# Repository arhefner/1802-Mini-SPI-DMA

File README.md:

# 1802-Mini-SPI-DMA
SPI Expansion Board for the 1802/Mini Computer

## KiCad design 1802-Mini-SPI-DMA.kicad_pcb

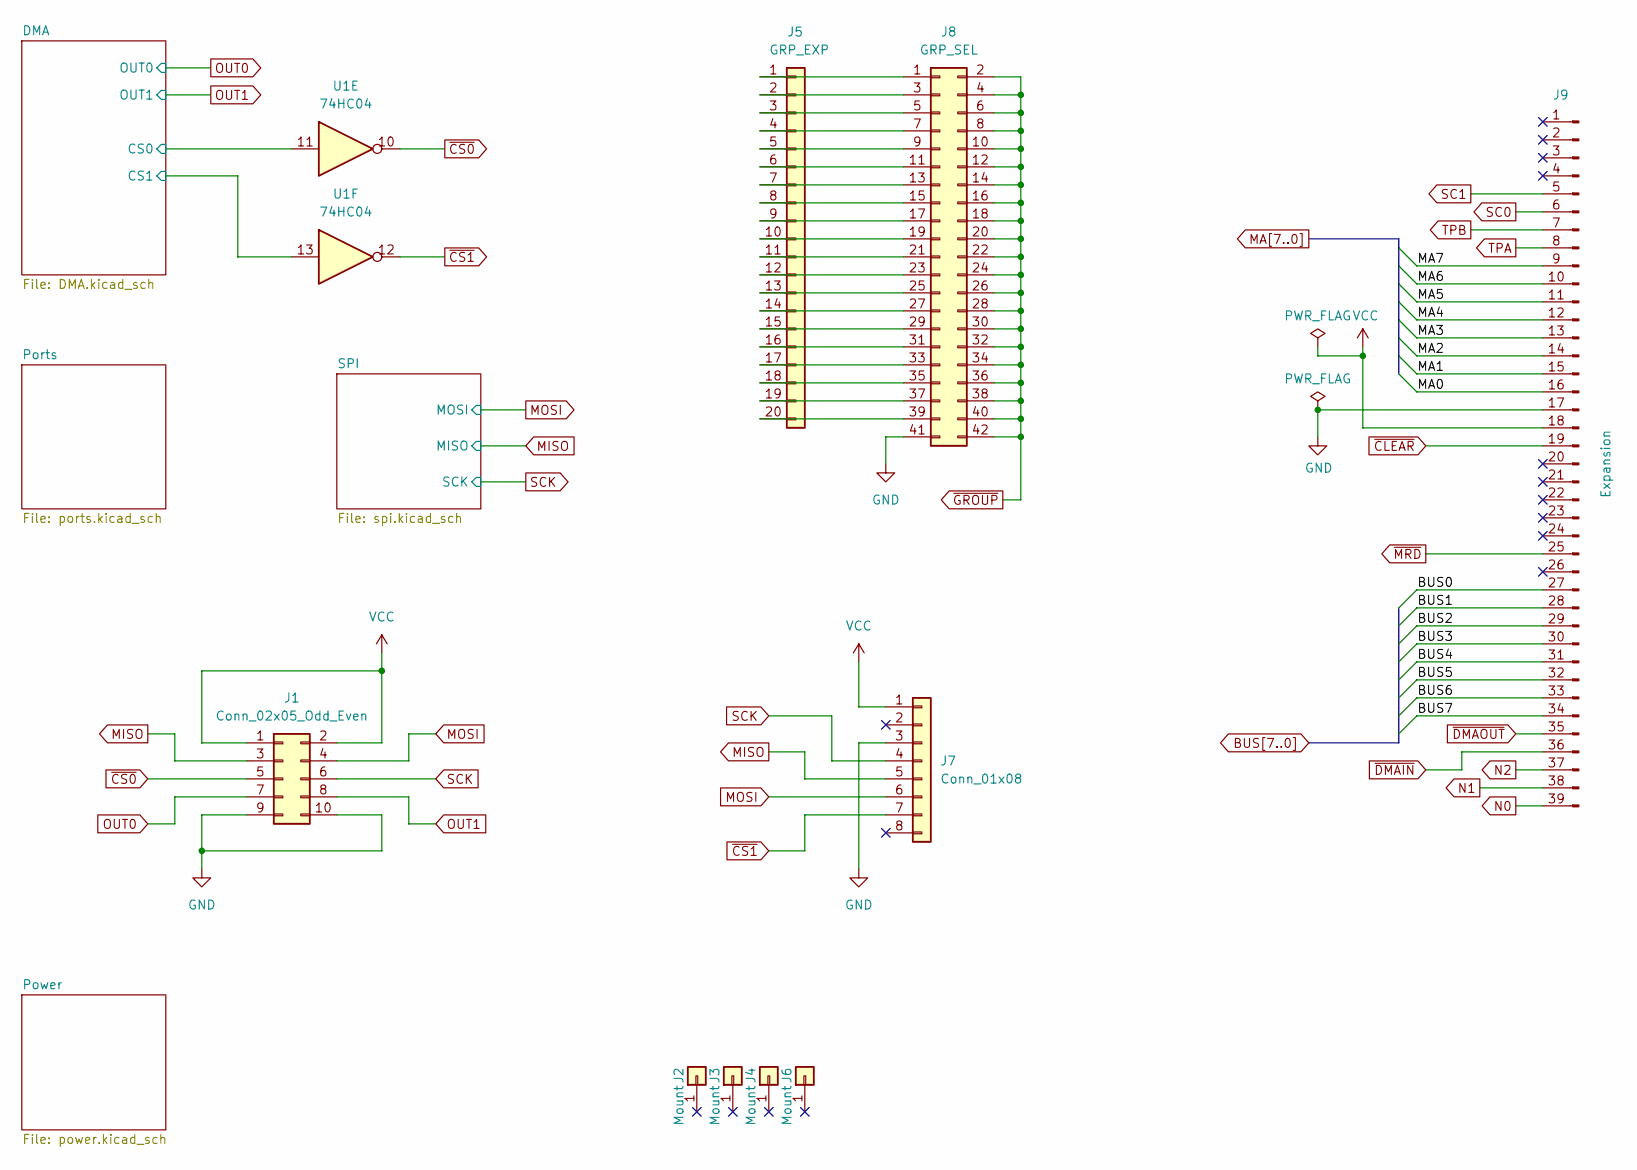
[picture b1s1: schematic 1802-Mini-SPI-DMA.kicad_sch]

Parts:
J1: Conn_02x05_Odd_Even; PinHeader_2x05_P2.54mm_Horizontal
J2, J3, J4, J6: Mount; 1pin
J5: GRP_EXP; PinHeader_1x20_P2.54mm_Vertical
J7: Conn_01x08; Adafruit_micro_sd_adapter
J8: GRP_SEL; PinHeader_2x21_P2.54mm_Vertical
J9: Expansion; Pin_Header_Straight_1x39_Pitch2.54mm
U1: 74HC04; DIP-14_W7.62mm_Socket

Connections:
/DMA/CS0: U1.11; also elsewhere on the board
/DMA/CS1: U1.13; also elsewhere on the board
BUS0: J9.27; also elsewhere on the board
BUS1: J9.28; also elsewhere on the board
BUS2: J9.29; also elsewhere on the board
BUS3: J9.30; also elsewhere on the board
BUS4: J9.31; also elsewhere on the board
BUS5: J9.32; also elsewhere on the board
BUS6: J9.33; also elsewhere on the board
BUS7: J9.34; also elsewhere on the board
GND: J1.9, J1.10, J7.3, J8.41, J9.17; also elsewhere on the board
MA0: J9.16
MA1: J9.15
MA2: J9.14
MA3: J9.13
MA4: J9.12
MA5: J9.11
MA6: J9.10
MA7: J9.9
MISO: J1.3, J7.5; also elsewhere on the board
MOSI: J1.4, J7.6; also elsewhere on the board
N0: J9.39; also elsewhere on the board
N1: J9.38; also elsewhere on the board
N2: J9.37; also elsewhere on the board
unnamed: J5.1, J8.1
unnamed: J5.2, J8.3
unnamed: J5.3, J8.5
unnamed: J5.4, J8.7
unnamed: J5.5, J8.9
unnamed: J5.6, J8.11
unnamed: J5.7, J8.13
unnamed: J5.8, J8.15
unnamed: J5.9, J8.17
unnamed: J5.10, J8.19
unnamed: J5.11, J8.21
unnamed: J5.12, J8.23
unnamed: J5.13, J8.25
unnamed: J5.14, J8.27
unnamed: J5.15, J8.29
unnamed: J5.16, J8.31
unnamed: J5.17, J8.33
unnamed: J5.18, J8.35
unnamed: J5.19, J8.37
unnamed: J5.20, J8.39
OUT0: J1.7; also elsewhere on the board
OUT1: J1.8; also elsewhere on the board
SC0: J9.6; also elsewhere on the board
SC1: J9.5; also elsewhere on the board
SCK: J1.6, J7.4; also elsewhere on the board
TPA: J9.8; also elsewhere on the board
TPB: J9.7; also elsewhere on the board
VCC: J1.1, J1.2, J7.1, J9.18; also elsewhere on the board
~CLEAR: J9.19; also elsewhere on the board
~CS0: J1.5, U1.10
~CS1: J7.7, U1.12
~DMAIN: J9.36; also elsewhere on the board
~DMAOUT: J9.35; also elsewhere on the board
~GROUP: J8.2, J8.4, J8.6, J8.8, J8.10, J8.12, J8.14, J8.16, J8.18, J8.20, J8.22, J8.24, J8.26, J8.28, J8.30, J8.32, J8.34, J8.36, J8.38, J8.40, J8.42; also elsewhere on the board
~MRD: J9.25; also elsewhere on the board

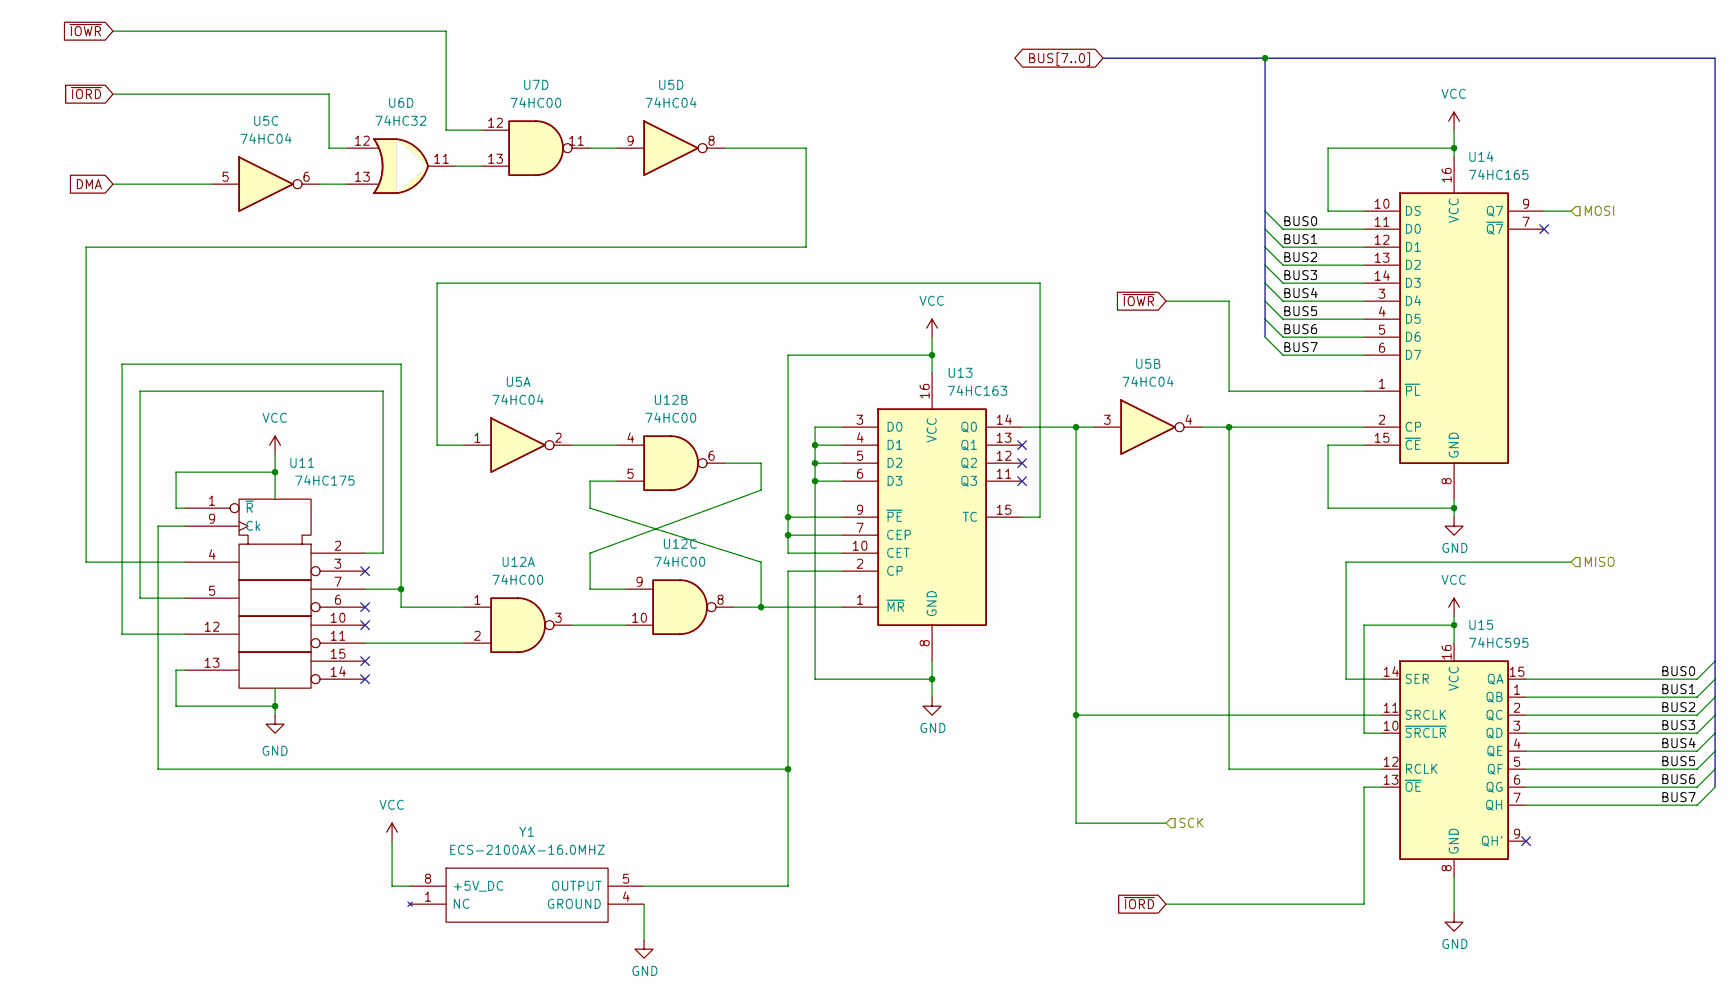
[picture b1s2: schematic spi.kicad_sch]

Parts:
U5: 74HC04; DIP-14_W7.62mm_Socket
U6: 74HC32; DIP-14_W7.62mm_Socket
U7, U12: 74HC00; DIP-14_W7.62mm_Socket
U11: 74HC175; DIP-16_W7.62mm_Socket
U13: 74HC163; DIP-16_W7.62mm_Socket
U14: 74HC165; DIP-16_W7.62mm_Socket
U15: 74HC595; DIP-16_W7.62mm_Socket
Y1: ECS-2100AX-16.0MHZ; ECS2100AX160MHZ; Mouser Part Number 520-TCH1600-X

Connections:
BUS0: U14.11 (D0), U15.15 (QA); also elsewhere on the board
BUS1: U14.12 (D1), U15.1 (QB); also elsewhere on the board
BUS2: U14.13 (D2), U15.2 (QC); also elsewhere on the board
BUS3: U14.14 (D3), U15.3 (QD); also elsewhere on the board
BUS4: U14.3 (D4), U15.4 (QE); also elsewhere on the board
BUS5: U14.4 (D5), U15.5 (QF); also elsewhere on the board
BUS6: U14.5 (D6), U15.6 (QG); also elsewhere on the board
BUS7: U14.6 (D7), U15.7 (QH); also elsewhere on the board
DMA: U5.5; also elsewhere on the board
GND: U11.8 (Vss), U11.13, U13.3 (D0), U13.4 (D1), U13.5 (D2), U13.6 (D3), U13.8 (GND), U14.8 (GND), U14.15 (~CE), U15.8 (GND), Y1.4 (GROUND); also elsewhere on the board
MISO: U15.14 (SER); also elsewhere on the board
MOSI: U14.9 (Q7); also elsewhere on the board
unnamed: U5.6, U6.13
unnamed: U5.9, U7.11
unnamed: U6.11, U7.13
unnamed: U11.2, U11.5
unnamed: U5.8, U11.4
unnamed: U11.9 (Ck), U13.2 (CP), Y1.5 (OUTPUT)
unnamed: U11.11, U12.2
unnamed: U11.7, U11.12, U12.1
unnamed: U5.2, U12.4
unnamed: U12.5, U12.8, U13.1 (~MR)
unnamed: U12.6, U12.9
unnamed: U12.3, U12.10
unnamed: U5.1, U13.15 (TC)
unnamed: U5.4, U14.2 (CP), U15.12 (RCLK)
SCK: U5.3, U13.14 (Q0), U15.11 (SRCLK); also elsewhere on the board
VCC: U11.1 (~R), U11.16 (Vdd), U13.7 (CEP), U13.9 (~PE), U13.10 (CET), U13.16 (VCC), U14.10 (DS), U14.16 (VCC), U15.10 (~SRCLR), U15.16 (VCC), Y1.8 (+5V_DC); also elsewhere on the board
~IORD: U6.12, U15.13 (~OE); also elsewhere on the board
~IOWR: U7.12, U14.1 (~PL); also elsewhere on the board

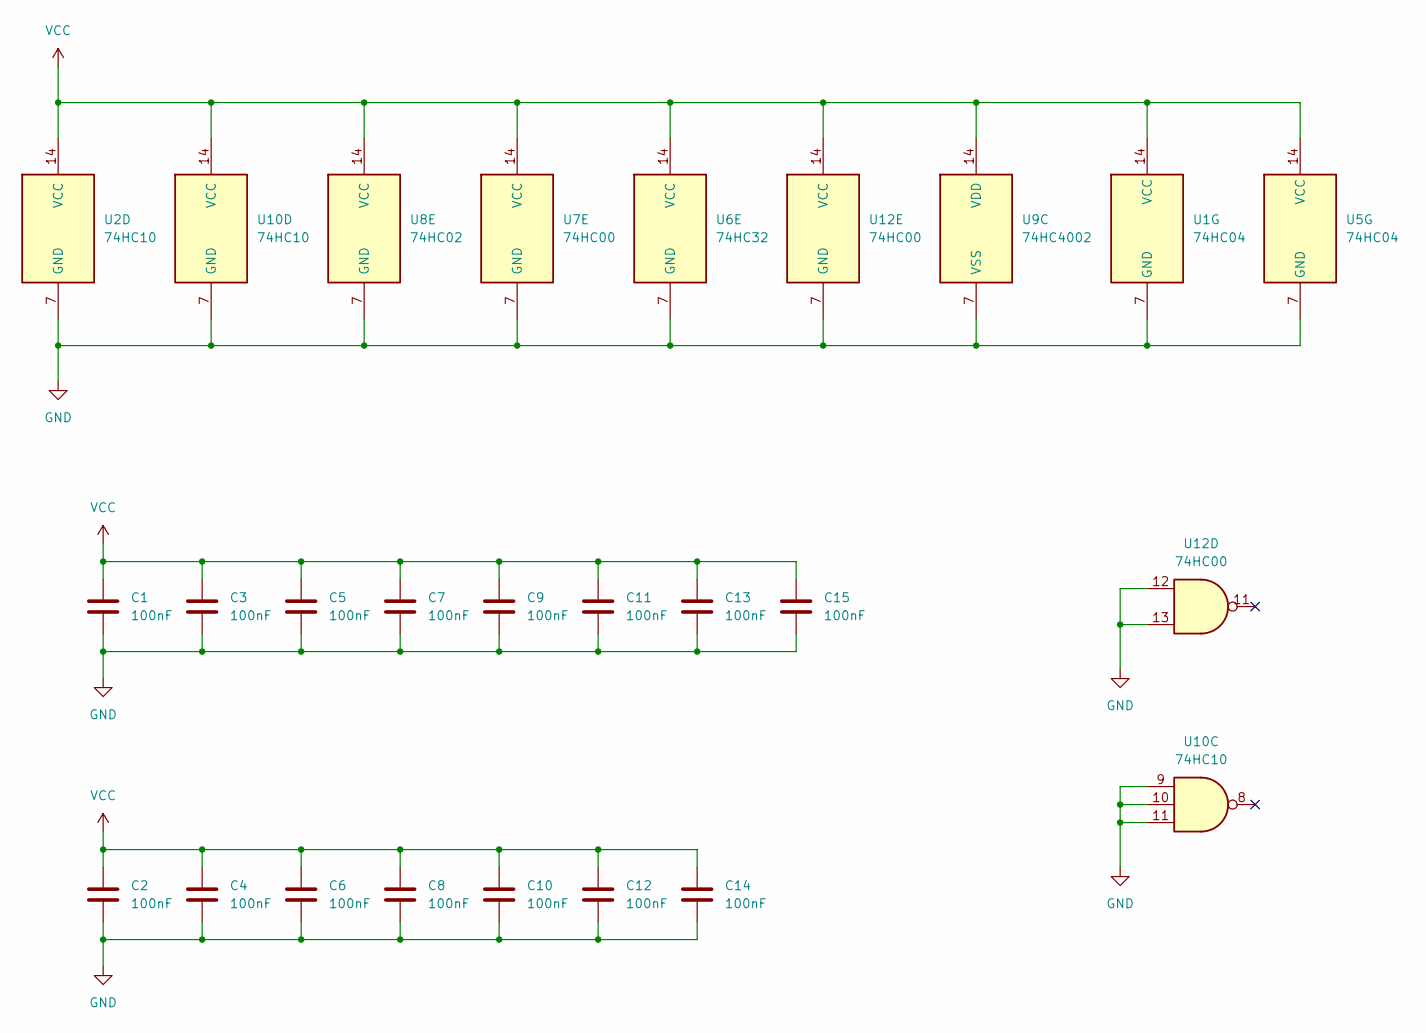
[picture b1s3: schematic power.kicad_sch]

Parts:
C1, C2, C3, C4, C5, C6, C7, C8, C9, C10, C11, C12, C13, C14, C15: 100nF; C_Disc_D4.7mm_W2.5mm_P5.00mm
U1, U5: 74HC04; DIP-14_W7.62mm_Socket
U2, U10: 74HC10; DIP-14_W7.62mm_Socket
U6: 74HC32; DIP-14_W7.62mm_Socket
U7, U12: 74HC00; DIP-14_W7.62mm_Socket
U8: 74HC02; DIP-14_W7.62mm_Socket
U9: 74HC4002; DIP-14_W7.62mm_Socket

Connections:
GND: C1.1, C2.1, C3.1, C4.1, C5.1, C6.1, C7.1, C8.1, C9.1, C10.1, C11.1, C12.1, C13.1, C14.1, C15.1, U1.7 (GND), U2.7 (GND), U5.7 (GND), U6.7 (GND), U7.7 (GND), U8.7 (GND), U9.7 (VSS), U10.7 (GND), U10.9, U10.10, U10.11, U12.7 (GND), U12.12, U12.13; also elsewhere on the board
VCC: C1.2, C2.2, C3.2, C4.2, C5.2, C6.2, C7.2, C8.2, C9.2, C10.2, C11.2, C12.2, C13.2, C14.2, C15.2, U1.14 (VCC), U2.14 (VCC), U5.14 (VCC), U6.14 (VCC), U7.14 (VCC), U8.14 (VCC), U9.14 (VDD), U10.14 (VCC), U12.14 (VCC); also elsewhere on the board

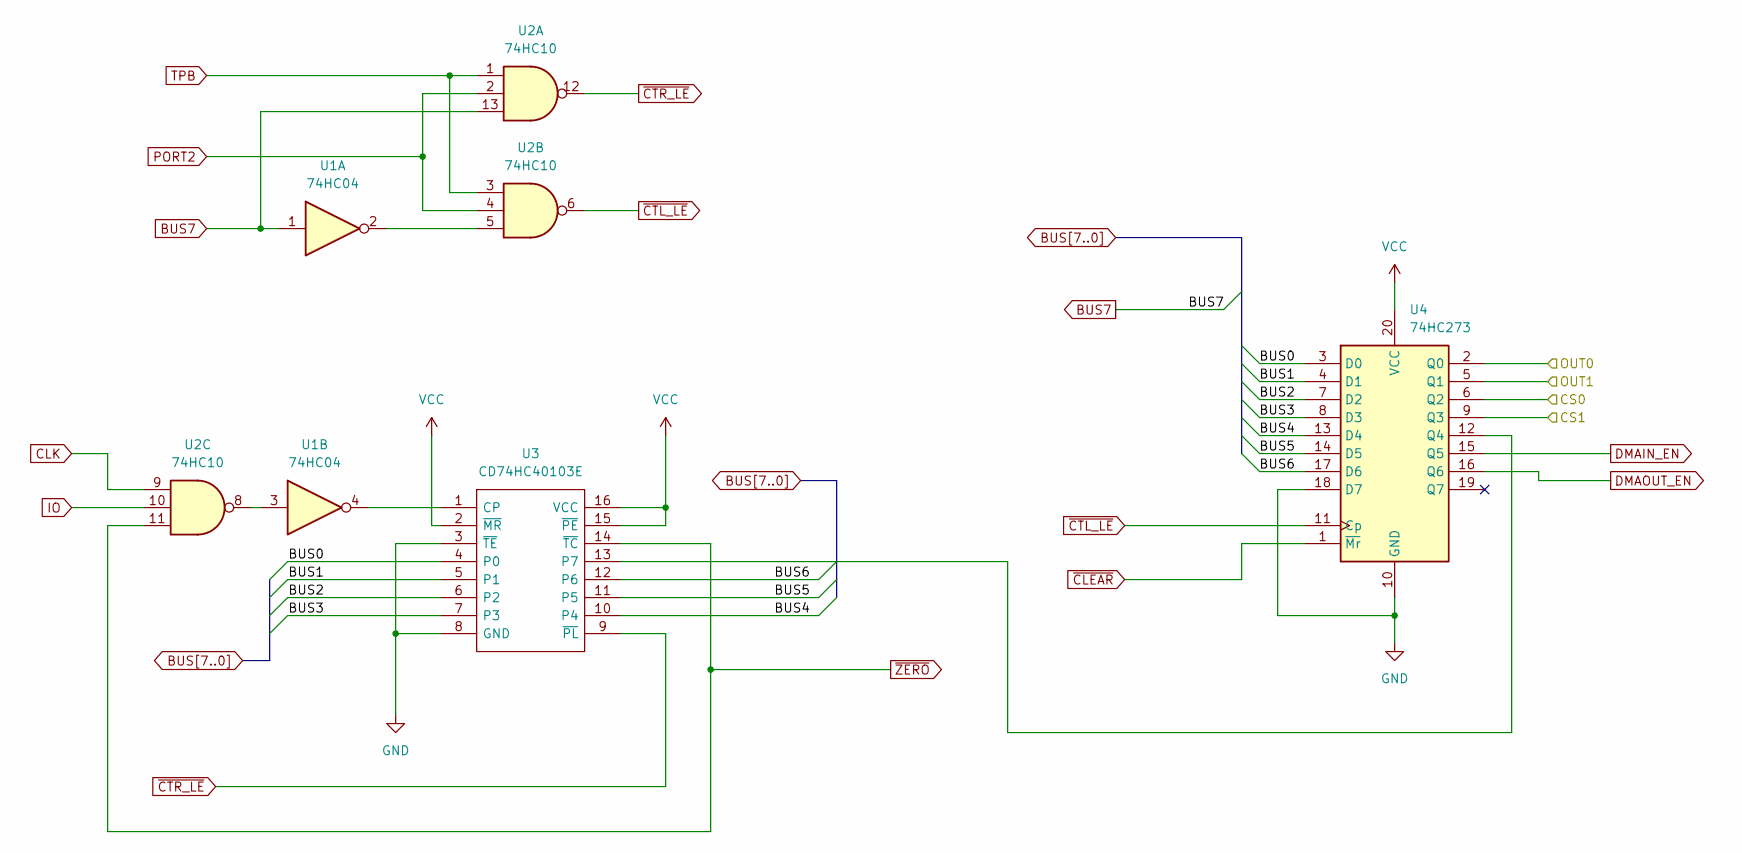
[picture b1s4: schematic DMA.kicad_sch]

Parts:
U1: 74HC04; DIP-14_W7.62mm_Socket
U2: 74HC10; DIP-14_W7.62mm_Socket
U3: CD74HC40103E; DIP-16_W7.62mm_Socket; Mouser Part Number 595-CD74HC40103E
U4: 74HC273; DIP-20_W7.62mm_Socket

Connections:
/DMA/CS0: U4.6 (Q2); also elsewhere on the board
/DMA/CS1: U4.9 (Q3); also elsewhere on the board
BUS0: U3.4 (P0), U4.3 (D0); also elsewhere on the board
BUS1: U3.5 (P1), U4.4 (D1); also elsewhere on the board
BUS2: U3.6 (P2), U4.7 (D2); also elsewhere on the board
BUS3: U3.7 (P3), U4.8 (D3); also elsewhere on the board
BUS4: U3.10 (P4), U4.13 (D4); also elsewhere on the board
BUS5: U3.11 (P5), U4.14 (D5); also elsewhere on the board
BUS6: U3.12 (P6), U4.17 (D6); also elsewhere on the board
BUS7: U1.1, U2.13; also elsewhere on the board
CLK: U2.9; also elsewhere on the board
DMAIN_EN: U4.15 (Q5); also elsewhere on the board
DMAOUT_EN: U4.16 (Q6); also elsewhere on the board
GND: U3.3 (~TE), U3.8 (GND), U4.10 (GND), U4.18 (D7); also elsewhere on the board
IO: U2.10; also elsewhere on the board
unnamed: U1.2, U2.5
unnamed: U1.3, U2.8
unnamed: U1.4, U3.1 (CP)
unnamed: U3.13 (P7), U4.12 (Q4)
OUT0: U4.2 (Q0); also elsewhere on the board
OUT1: U4.5 (Q1); also elsewhere on the board
PORT2: U2.2, U2.4; also elsewhere on the board
TPB: U2.1, U2.3; also elsewhere on the board
VCC: U3.2 (~MR), U3.15 (~PE), U3.16 (VCC), U4.20 (VCC); also elsewhere on the board
~CLEAR: U4.1 (~Mr); also elsewhere on the board
~CTL_LE: U2.6, U4.11 (Cp)
~CTR_LE: U2.12, U3.9 (~PL)
~ZERO: U2.11, U3.14 (~TC); also elsewhere on the board

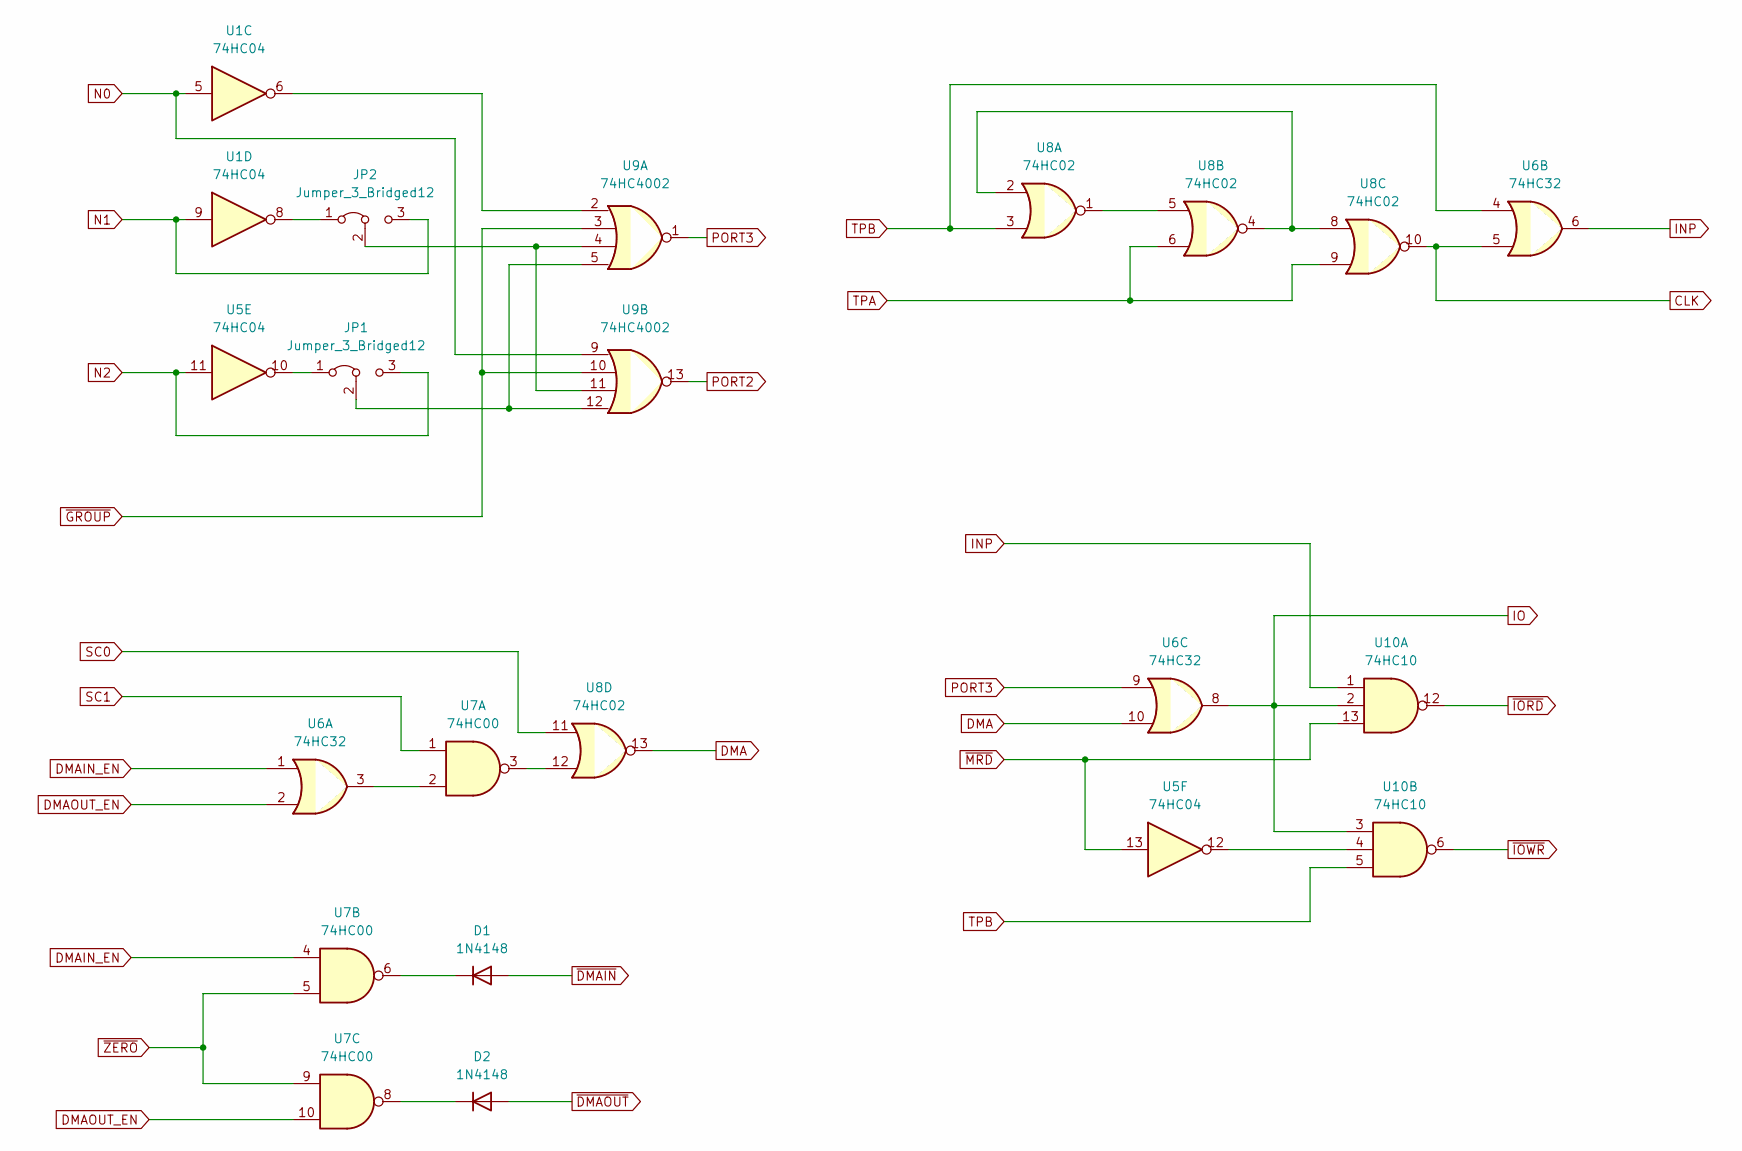
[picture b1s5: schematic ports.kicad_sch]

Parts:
D1, D2: 1N4148; D_DO-35_SOD27_P7.62mm_Horizontal
JP1, JP2: Jumper_3_Bridged12; PinHeader_1x03_P2.54mm_Vertical
U1, U5: 74HC04; DIP-14_W7.62mm_Socket
U6: 74HC32; DIP-14_W7.62mm_Socket
U7: 74HC00; DIP-14_W7.62mm_Socket
U8: 74HC02; DIP-14_W7.62mm_Socket
U9: 74HC4002; DIP-14_W7.62mm_Socket
U10: 74HC10; DIP-14_W7.62mm_Socket

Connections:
CLK: U6.5, U8.10; also elsewhere on the board
DMA: U6.10, U8.13; also elsewhere on the board
DMAIN_EN: U6.1, U7.4; also elsewhere on the board
DMAOUT_EN: U6.2, U7.10; also elsewhere on the board
INP: U6.6, U10.1
IO: U6.8, U10.2, U10.3; also elsewhere on the board
N0: U1.5, U9.9; also elsewhere on the board
N1: JP2.3 (B), U1.9; also elsewhere on the board
N2: JP1.3 (B), U5.11; also elsewhere on the board
unnamed: D1.1 (K), U7.6
unnamed: D2.1 (K), U7.8
unnamed: JP1.1 (A), U5.10
unnamed: JP1.2 (C), U9.5, U9.12
unnamed: JP2.1 (A), U1.8
unnamed: JP2.2 (C), U9.4, U9.11
unnamed: U1.6, U9.2
unnamed: U6.3, U7.2
unnamed: U7.3, U8.12
unnamed: U8.1, U8.5
unnamed: U8.2, U8.4, U8.8
unnamed: U5.12, U10.4
PORT2: U9.13; also elsewhere on the board
PORT3: U6.9, U9.1
SC0: U8.11; also elsewhere on the board
SC1: U7.1; also elsewhere on the board
TPA: U8.6, U8.9; also elsewhere on the board
TPB: U6.4, U8.3, U10.5; also elsewhere on the board
~DMAIN: D1.2 (A); also elsewhere on the board
~DMAOUT: D2.2 (A); also elsewhere on the board
~GROUP: U9.3, U9.10; also elsewhere on the board
~IORD: U10.12; also elsewhere on the board
~IOWR: U10.6; also elsewhere on the board
~MRD: U5.13, U10.13; also elsewhere on the board
~ZERO: U7.5, U7.9; also elsewhere on the board

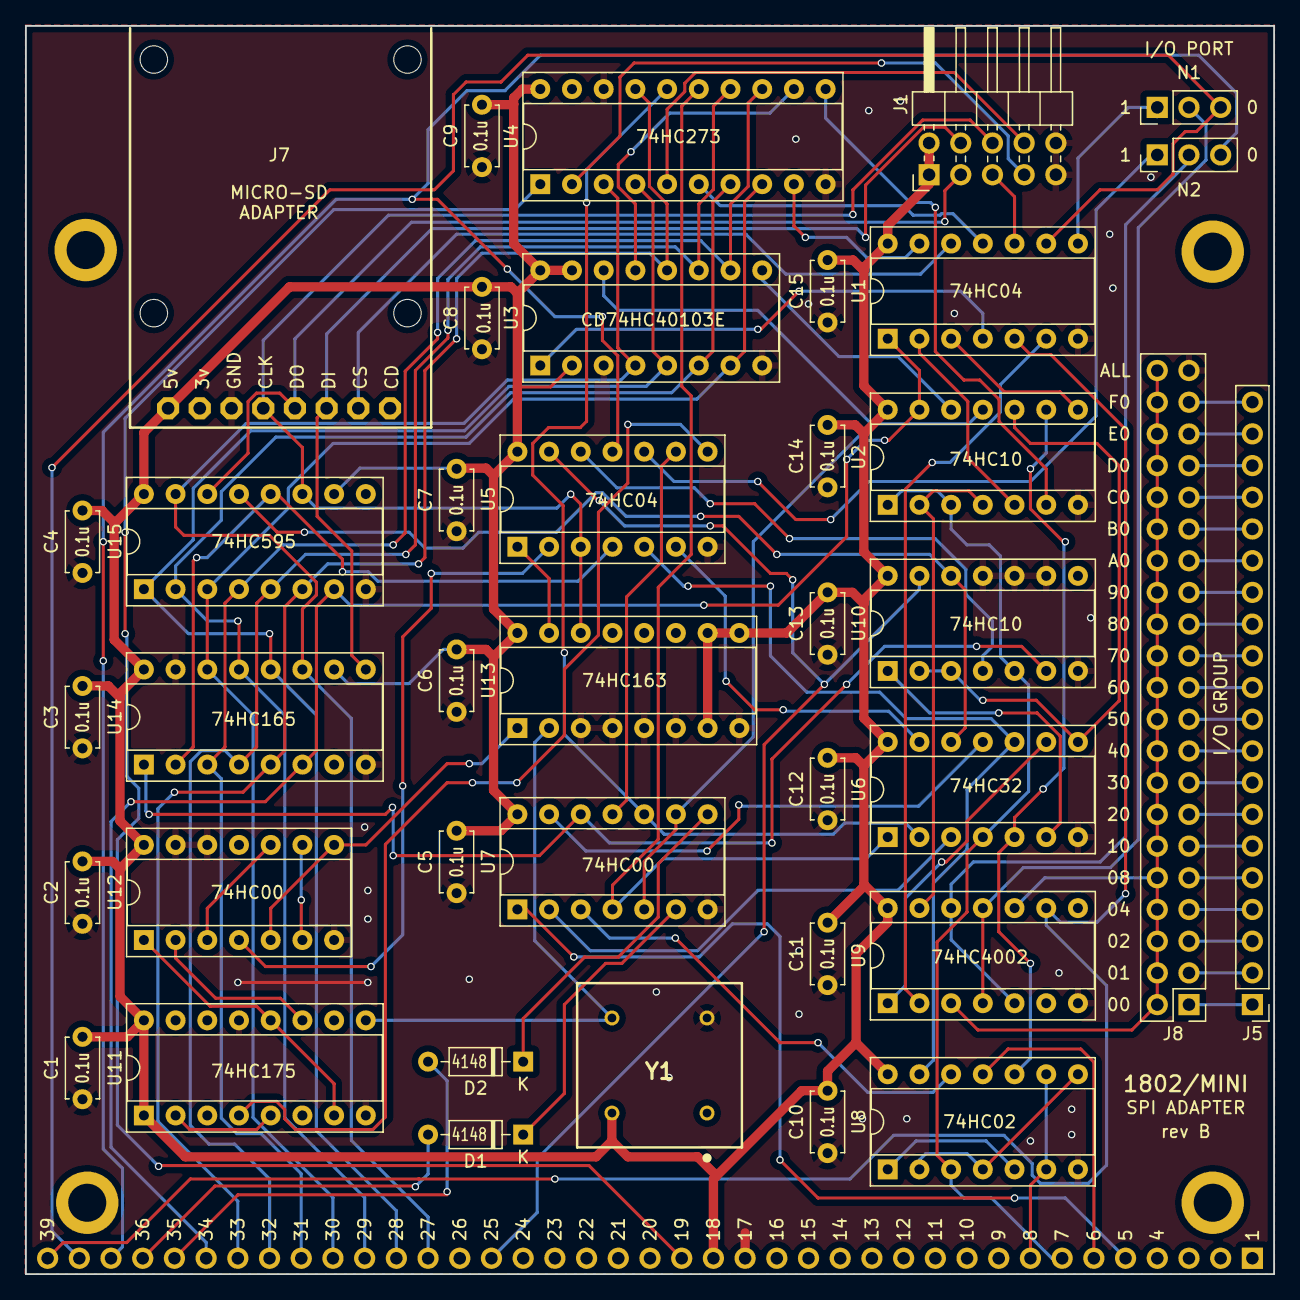
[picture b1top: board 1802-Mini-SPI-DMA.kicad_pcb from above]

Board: 2 copper layers, 100.0 x 100.0 mm, 44 parts (0 on the bottom side), 94 nets.

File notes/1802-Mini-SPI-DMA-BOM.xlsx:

Please refer to these notes as applicable for the parts list below:
*A | The Samtec 39 pin connector, when ordering from Digikey, will always show zero 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
*B | These parts may be omitted if group port selection will not be used. See assemb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
*C | Use the long tail headers for stacked assembly, and the right-angle headers if 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
SPI INTERFACE
Qty | Description |  | Manufacturer | Manufacturer # | Vendor | Vendor # | Price | Qty | Total
Integrated Circuits
2 | 74HC04 | U1,U5 | TI | CD74HC04E | Digikey | 296-12772-5-ND | 0.68 | 2 | 1.36
2 | 74HC10 | U2,U10 | TI | SN74HC10N | Digikey | 296-8214-5-ND | 0.65 | 2 | 1.3
1 | 74HC40103 | U3 | TI | CD74HC40103E | Digikey | 296-9200-5-ND | 1.85 | 1 | 1.85
1 | 74HC273 | U4 | TI | CD74HC273E | Digikey | 296-12801-5-ND | 0.93 | 1 | 0.93
1 | 74HC32 | U6 | TI | SN74HC32N | Digikey | 296-1589-5-ND | 0.6 | 1 | 0.6
2 | 74HC00 | U7,U12 | TI | SN74HC00N | Digikey | 296-1563-5-ND | 0.6 | 2 | 1.2
1 | 74HC02 | U8 | TI | CD74HC02E | Digikey | 296-12770-5-ND | 0.5 | 1 | 0.5
1 | 74HC4002 | U9 | TI | CD74HC4002E | Digikey | 296-25987-5-ND | 0.68 | 1 | 0.68
1 | 74HC175 | U11 | TI | SN74HC175N | Digikey | 296-8257-5-ND | 0.93 | 1 | 0.93
1 | 74HC163 | U13 | TI | SN74HC163N | Digikey | 296-8246-5-ND | 0.92 | 1 | 0.92
1 | 74HC165 | U14 | TI | SN74HC165N | Digikey | 296-8251-5-ND | 0.6 | 1 | 0.6
1 | 74AHCT595 | U15 | TI | SN74AHCT595N | Digikey | 296-33695-5-ND | 0.76 | 1 | 0.76
Discrete Components
2 | Diode 1N4148 | D1,D2 | ON Semi | 1N4148 | Digikey | 1N4148FS-ND | 0.1 | 2 | 0.2
15 | Ceramic capacitor 0.1uF radial 0.2" | C1-15 | Vishay | K104K10X7RF5UH5 | Digikey | BC2665CT-ND | 0.156 | 15 | 2.34
1 | XTAL OSC XO 16.0000MHZ HCMOS TTL | Y1 | ECS Inc. | ECS-2100AX-160 | Digikey | X963-ND | 3.15 | 1 | 3.15
1 | MICROSD CARD BREAKOUT 5V OR 3V | J7 | Adafruit | 254 | Digikey | 1528-1462-ND | 7.5 | 1 | 7.5
Interconnects
1 | R/A shrouded header 10 pins 0.1" | J1 | Hirose | HIF3FC-10PA-2.54DS(71) | Digikey | H123842-ND | 2.21 | 1 | 2.21
2 | Straight header 3 pins 0.1" |  | Sullins | PREC003SAAN-RC | Digikey | S1012EC-03-ND | 0.09 | 2 | 0.18
1 | Straight header 8 pins 0.1" | J7 | Sullins | PREC008SAAN-RC | Digikey | S1012EC-08-ND | 0.19 | 1 | 0.19
1 | Straight dual row header 21 position (*B) | J8 | Sullins | PREC021DAAN-RC | Digikey | S2012EC-21-ND | 0.73 | 1 | 0.73
3 | Jumper shunts 0.1" |  | Sullins | STC02SYAN | Digikey | S9000-ND | 0.09 | 3 | 0.27
1 | Socket 39 pin 0.1" long tail (*A)(*C) |  | Samtec | SSQ-139-03-T-S | Digikey | SAM1206-39-ND | 6.47 | 1 | 6.47
1 | Socket 20 pin 0.1" long tail (*B)(*C) |  | Samtec | SSQ-120-03-T-S | Digikey | SAM1206-20-ND | 3.46 | 1 | 3.46
1 | R/A header 39 pin 0.1" (*C) |  | Sullins | PREC039SBAN-M71RC | Digikey | S1112EC-39-ND | 0.88 | 1 | 0.88
1 | R/A header 20 pin 0.1" (*C) |  | Sullins | PREC020SBAN-M71RC | Digikey | S1112EC-20-ND | 0.5 | 1 | 0.5
Sockets
1 | DIP socket 8 pin 0.3" |  | On Shore | ED08DT | Digikey | ED3044-5-ND | 0.21 | 1 | 0.21
9 | DIP socket 14 pin 0.3" |  | On Shore | ED14DT | Digikey | ED3045-5-ND | 0.19 | 9 | 1.71
5 | DIP socket 16 pin 0.3" |  | On Shore | ED16DT | Digikey | ED3046-5-ND | 0.26 | 5 | 1.3
1 | DIP socket 20 pin 0.3" |  | On Shore | ED20DT | Digikey | ED3054-5-ND | 0.31 | 1 | 0.31
Mechanical
4 | 0.5 inch standoff spacer |  | RAF | 4505-440-AL-7 | Jameco | 393474 | 0.49 | 4 | 1.96
1 | Circuit Board |  | Hefner |  | JLCPCB |  | 0.4 | 1 | 0.4
 |  |  |  |  |  |  | Total |  | 45.6

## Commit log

2022-10-27 Initial commit of project.
2022-11-29 Add BOM and errata
2022-12-16 Update silk screen.
